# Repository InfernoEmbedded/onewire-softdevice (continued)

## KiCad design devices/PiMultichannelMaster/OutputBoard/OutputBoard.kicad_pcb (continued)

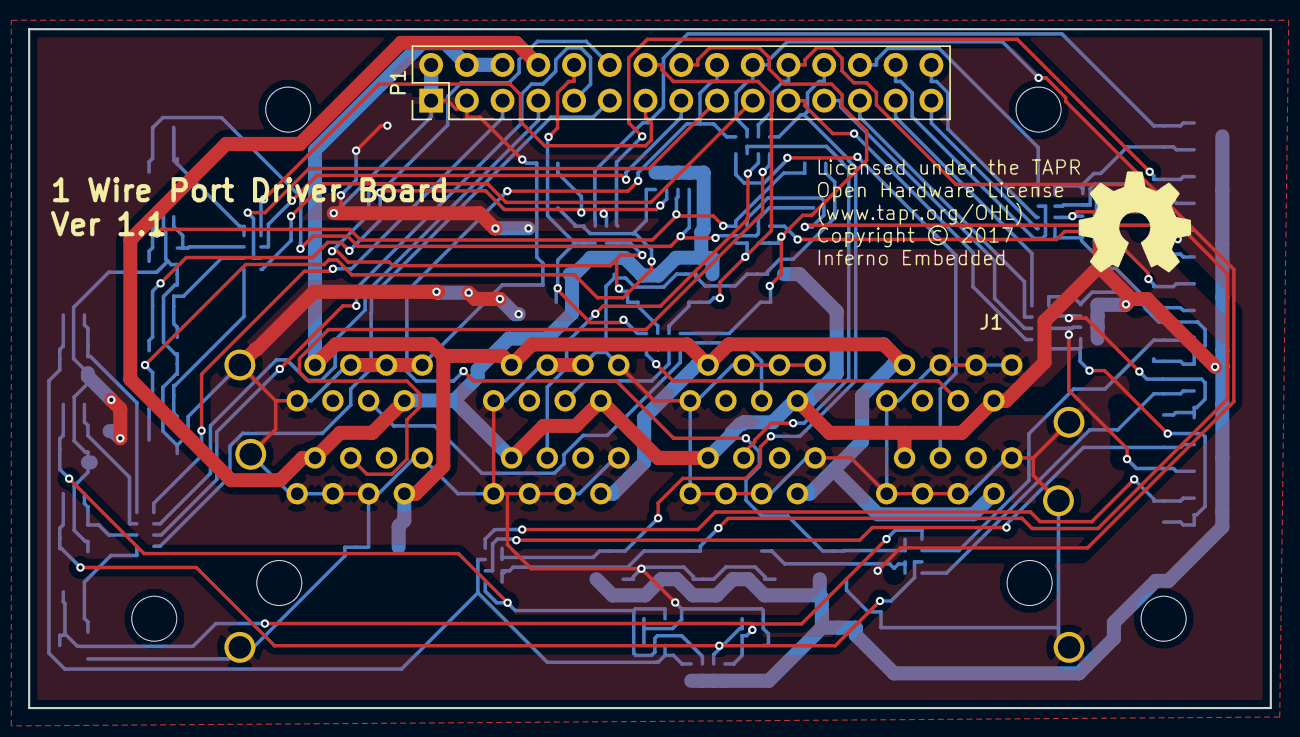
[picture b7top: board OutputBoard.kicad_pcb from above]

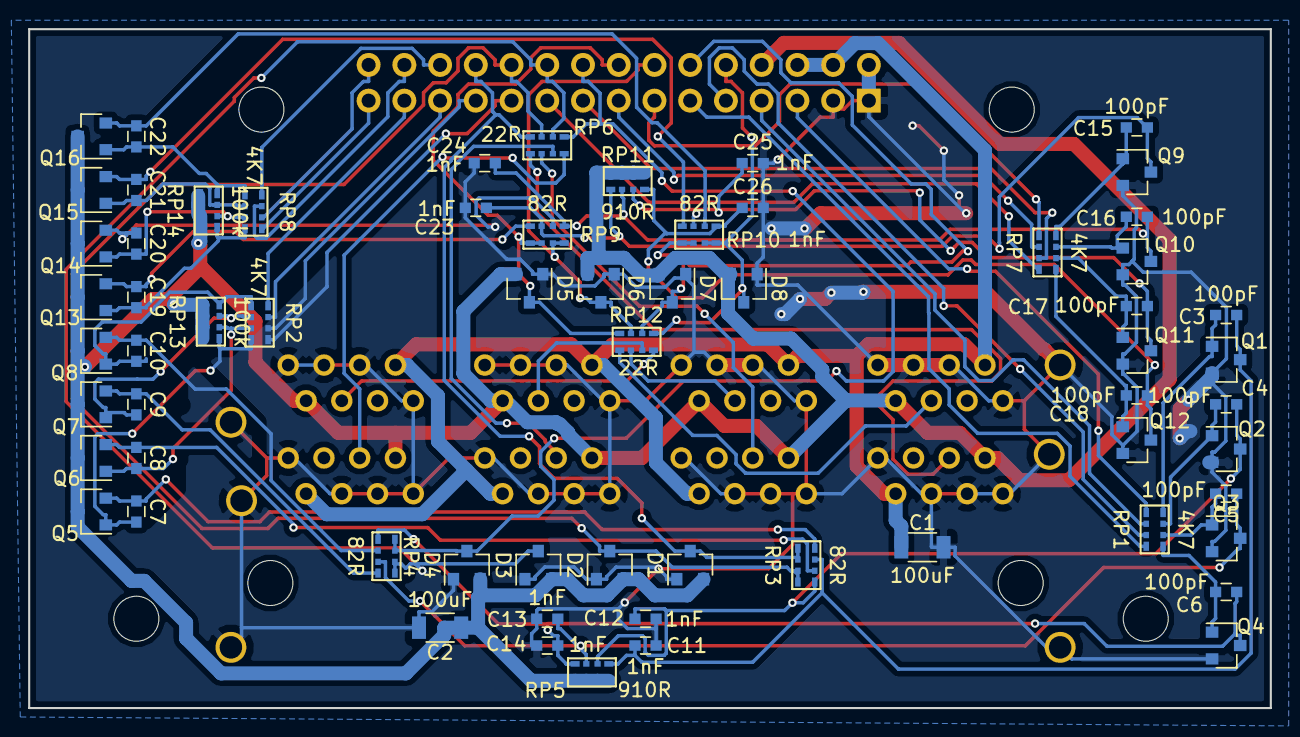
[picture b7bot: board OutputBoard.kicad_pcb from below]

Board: 2 copper layers, 88.3 x 48.3 mm, 70 parts (64 on the bottom side), 67 nets.

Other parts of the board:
REF0, REF1, REF3, REF4: MountingHole_3.2mm_M3
